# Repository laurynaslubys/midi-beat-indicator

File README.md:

Playing around with Arduino and MIDI. See
[my blog post](https://laurynasl.lt/blog/playing-around-with-arduino-and-midi)
for more details.

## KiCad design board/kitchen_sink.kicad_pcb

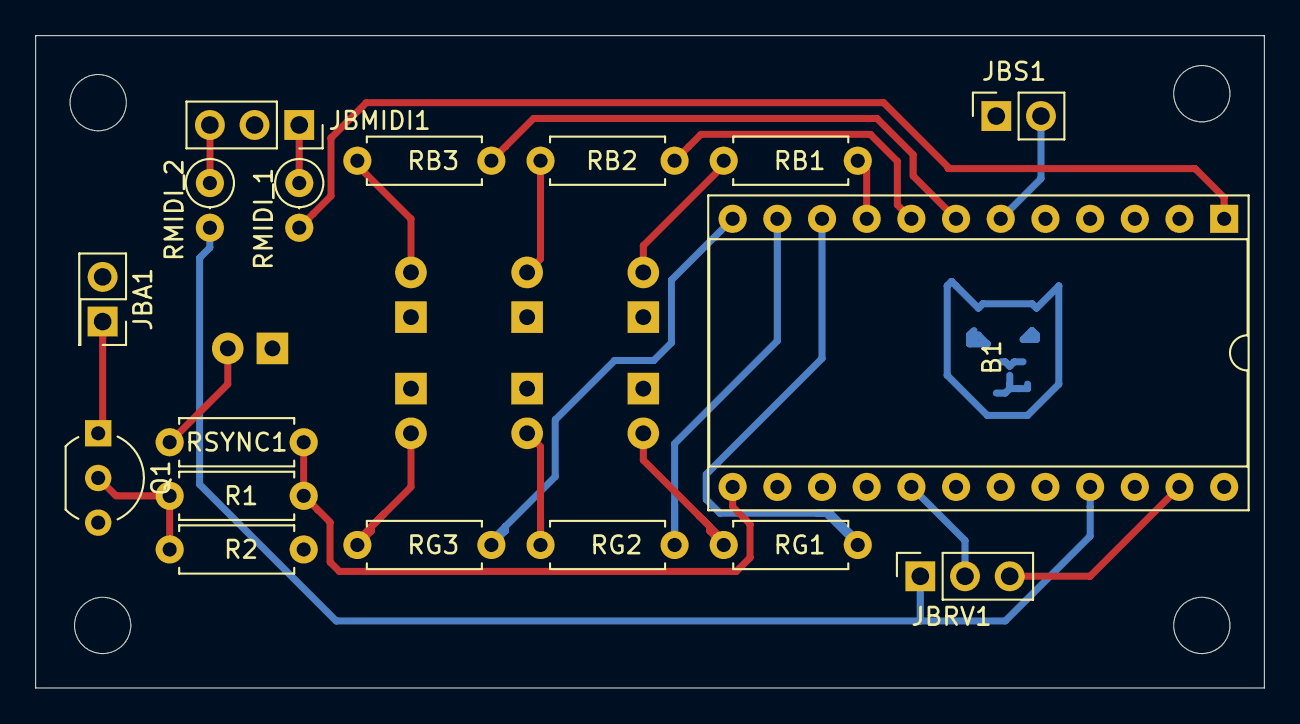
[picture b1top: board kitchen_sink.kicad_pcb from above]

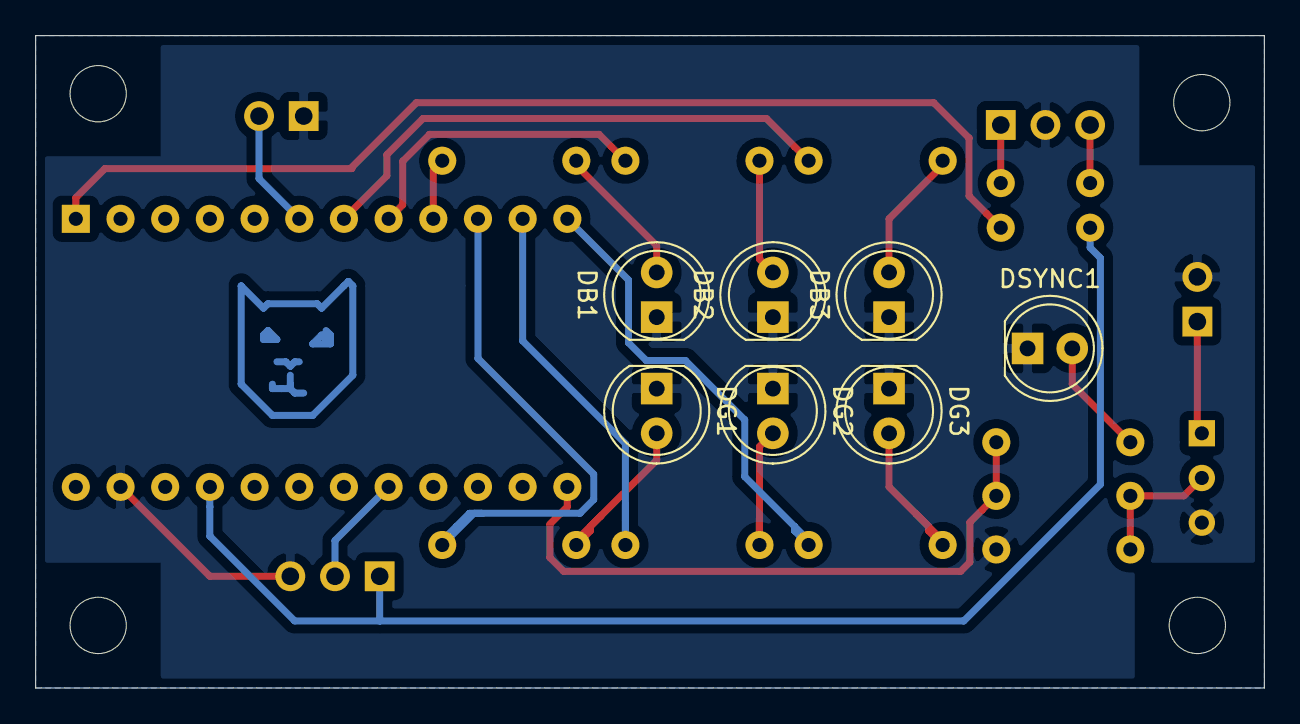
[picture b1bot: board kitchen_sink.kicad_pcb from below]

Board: 2 copper layers, 69.9 x 37.1 mm, 28 parts (7 on the bottom side), 23 nets.

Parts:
B1: SPARKFUN_PRO_MICRO; DIP-24_W15.24mm_Socket
DB1, DB2, DB3: BLUE; LED_D5.0mm
DG1, DG2, DG3: LED; LED_D5.0mm
DSYNC1: RED; LED_D5.0mm
H1, H2, H3, H4: MountingHole_3.2mm_M3
JBA1: Conn_01x02_Female; PinSocket_2x01_P2.54mm_Vertical
JBMIDI1: Conn_01x03_Female; PinSocket_1x03_P2.54mm_Vertical
JBRV1: Conn_01x03_Female; PinSocket_1x03_P2.54mm_Vertical
JBS1: Conn_01x02_Female; PinSocket_1x02_P2.54mm_Vertical
Q1: TRANS_NPN-P2N2222A; TO-92_Inline_Wide
R1: 10k; R_Axial_DIN0207_L6.3mm_D2.5mm_P7.62mm_Horizontal
R2: 4.7k; R_Axial_DIN0207_L6.3mm_D2.5mm_P7.62mm_Horizontal
RB1, RB2, RB3: 1k; R_Axial_DIN0207_L6.3mm_D2.5mm_P7.62mm_Horizontal
RG1, RG2, RG3: 1k; R_Axial_DIN0207_L6.3mm_D2.5mm_P7.62mm_Horizontal
RMIDI_1, RMIDI_2: 220; R_Axial_DIN0207_L6.3mm_D2.5mm_P2.54mm_Vertical
RSYNC1: 4.7k; R_Axial_DIN0207_L6.3mm_D2.5mm_P7.62mm_Horizontal

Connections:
GND: B1.23, DB1.1, DB2.1, DB3.1, DG1.1, DG2.1, DG3.1, DSYNC1.1, JBA1.2, JBMIDI1.2, JBRV1.3, JBS1.1, Q1.3, R2.1
unnamed: B1.1, RMIDI_1.2
unnamed: B1.6, JBS1.2
unnamed: B1.7, RB3.1
unnamed: B1.8, RB2.1
unnamed: B1.9, RB1.1
unnamed: B1.10, RG1.1
unnamed: B1.11, RG2.1
unnamed: B1.12, RG3.1
unnamed: B1.13, R1.2, RSYNC1.1
unnamed: B1.17, JBRV1.2
unnamed: DB1.2, RB1.2
unnamed: DB2.2, RB2.2
unnamed: DB3.2, RB3.2
unnamed: DG1.2, RG1.2
unnamed: DG2.2, RG2.2
unnamed: DG3.2, RG3.2
unnamed: DSYNC1.2, RSYNC1.2
unnamed: JBA1.1, Q1.1
unnamed: JBMIDI1.1, RMIDI_1.1
unnamed: JBMIDI1.3, RMIDI_2.1
unnamed: Q1.2, R1.1, R2.2
VCC: B1.21, JBRV1.1, RMIDI_2.2

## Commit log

2020-09-24 it's alive!
2020-09-24 Calculate note correctly
2020-10-16 Sorta works
2020-10-17 Very blinky
2020-10-19 Introduce queue for midi
2020-10-19 Use encoder
2020-10-19 WIP bpm counter]
2020-10-21 Use different midi lib
2020-10-23 Add midi out, support for pro micro
2020-10-25 Schematics + wiring for PCB version
2020-10-25 Add readme
2020-10-25 Underp readme
